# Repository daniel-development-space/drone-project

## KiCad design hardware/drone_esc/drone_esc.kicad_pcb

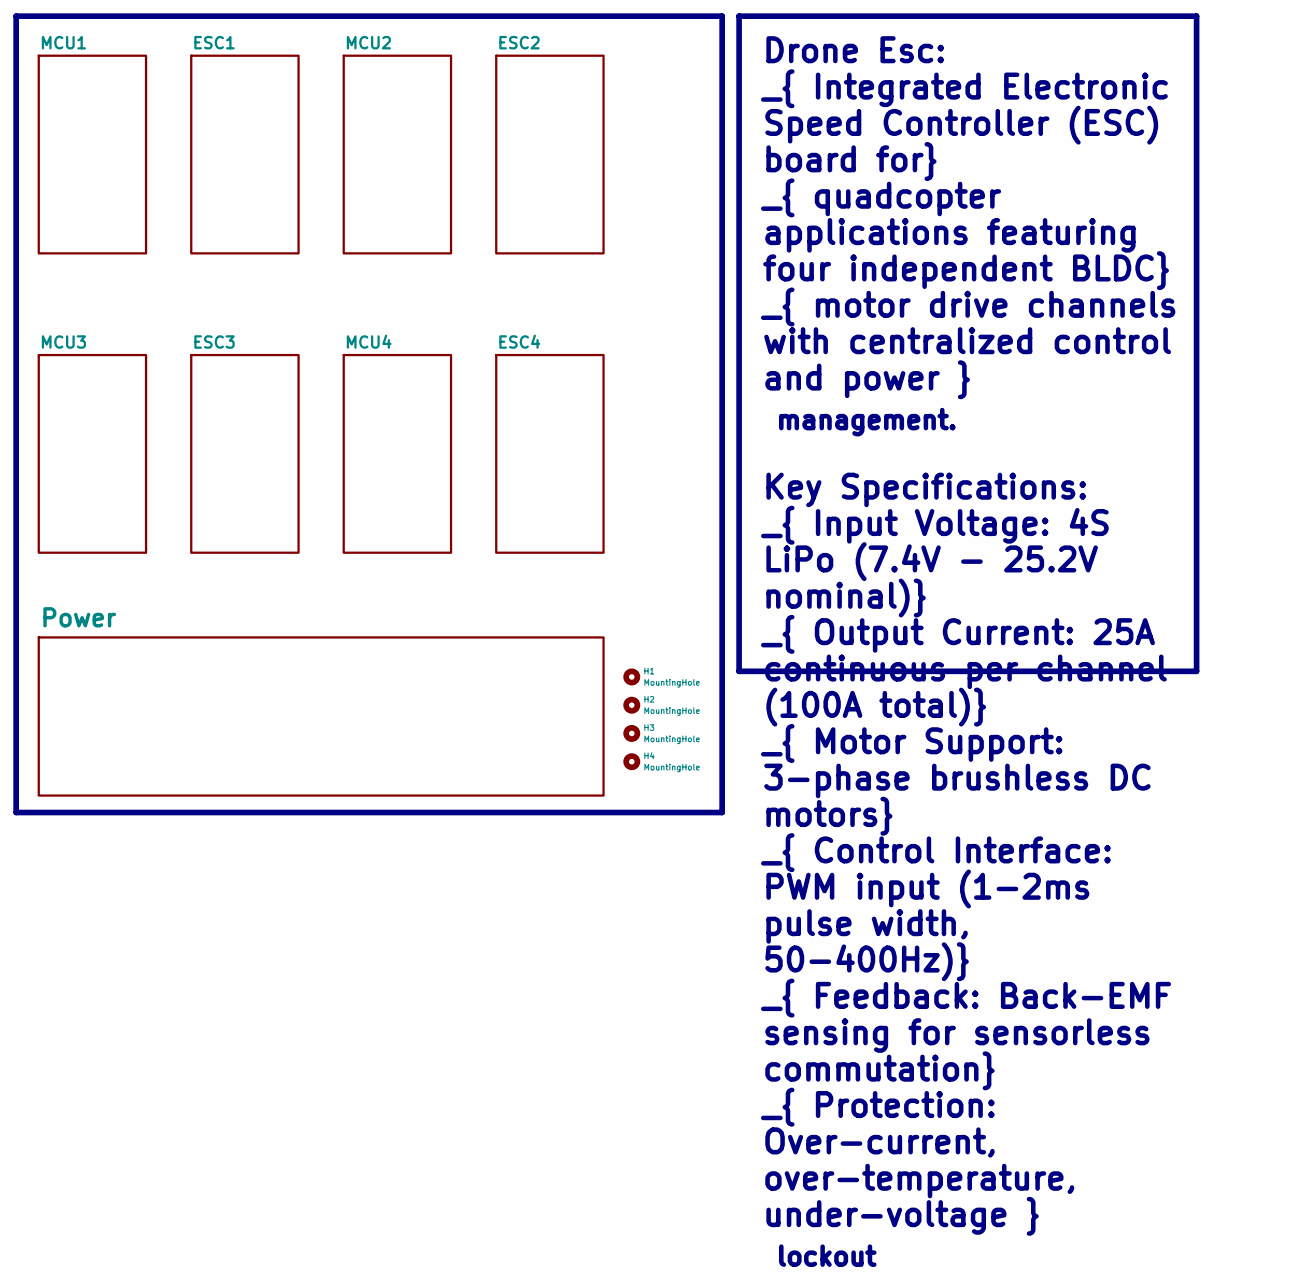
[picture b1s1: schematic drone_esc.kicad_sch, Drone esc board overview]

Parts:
H1, H2, H3, H4: MountingHole; MountingHole_3.2mm_M3

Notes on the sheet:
Drone Esc: _{ Integrated Electronic Speed Controller (ESC) board for} _{ quadcopter applications featuring four independent BLDC} _{ motor drive channels with centralized control and power } _{ management.} Key Specifications: _{ Input Voltage: 4S LiPo (7.4V - 25.2V nominal)} _{ Output Current: 25A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

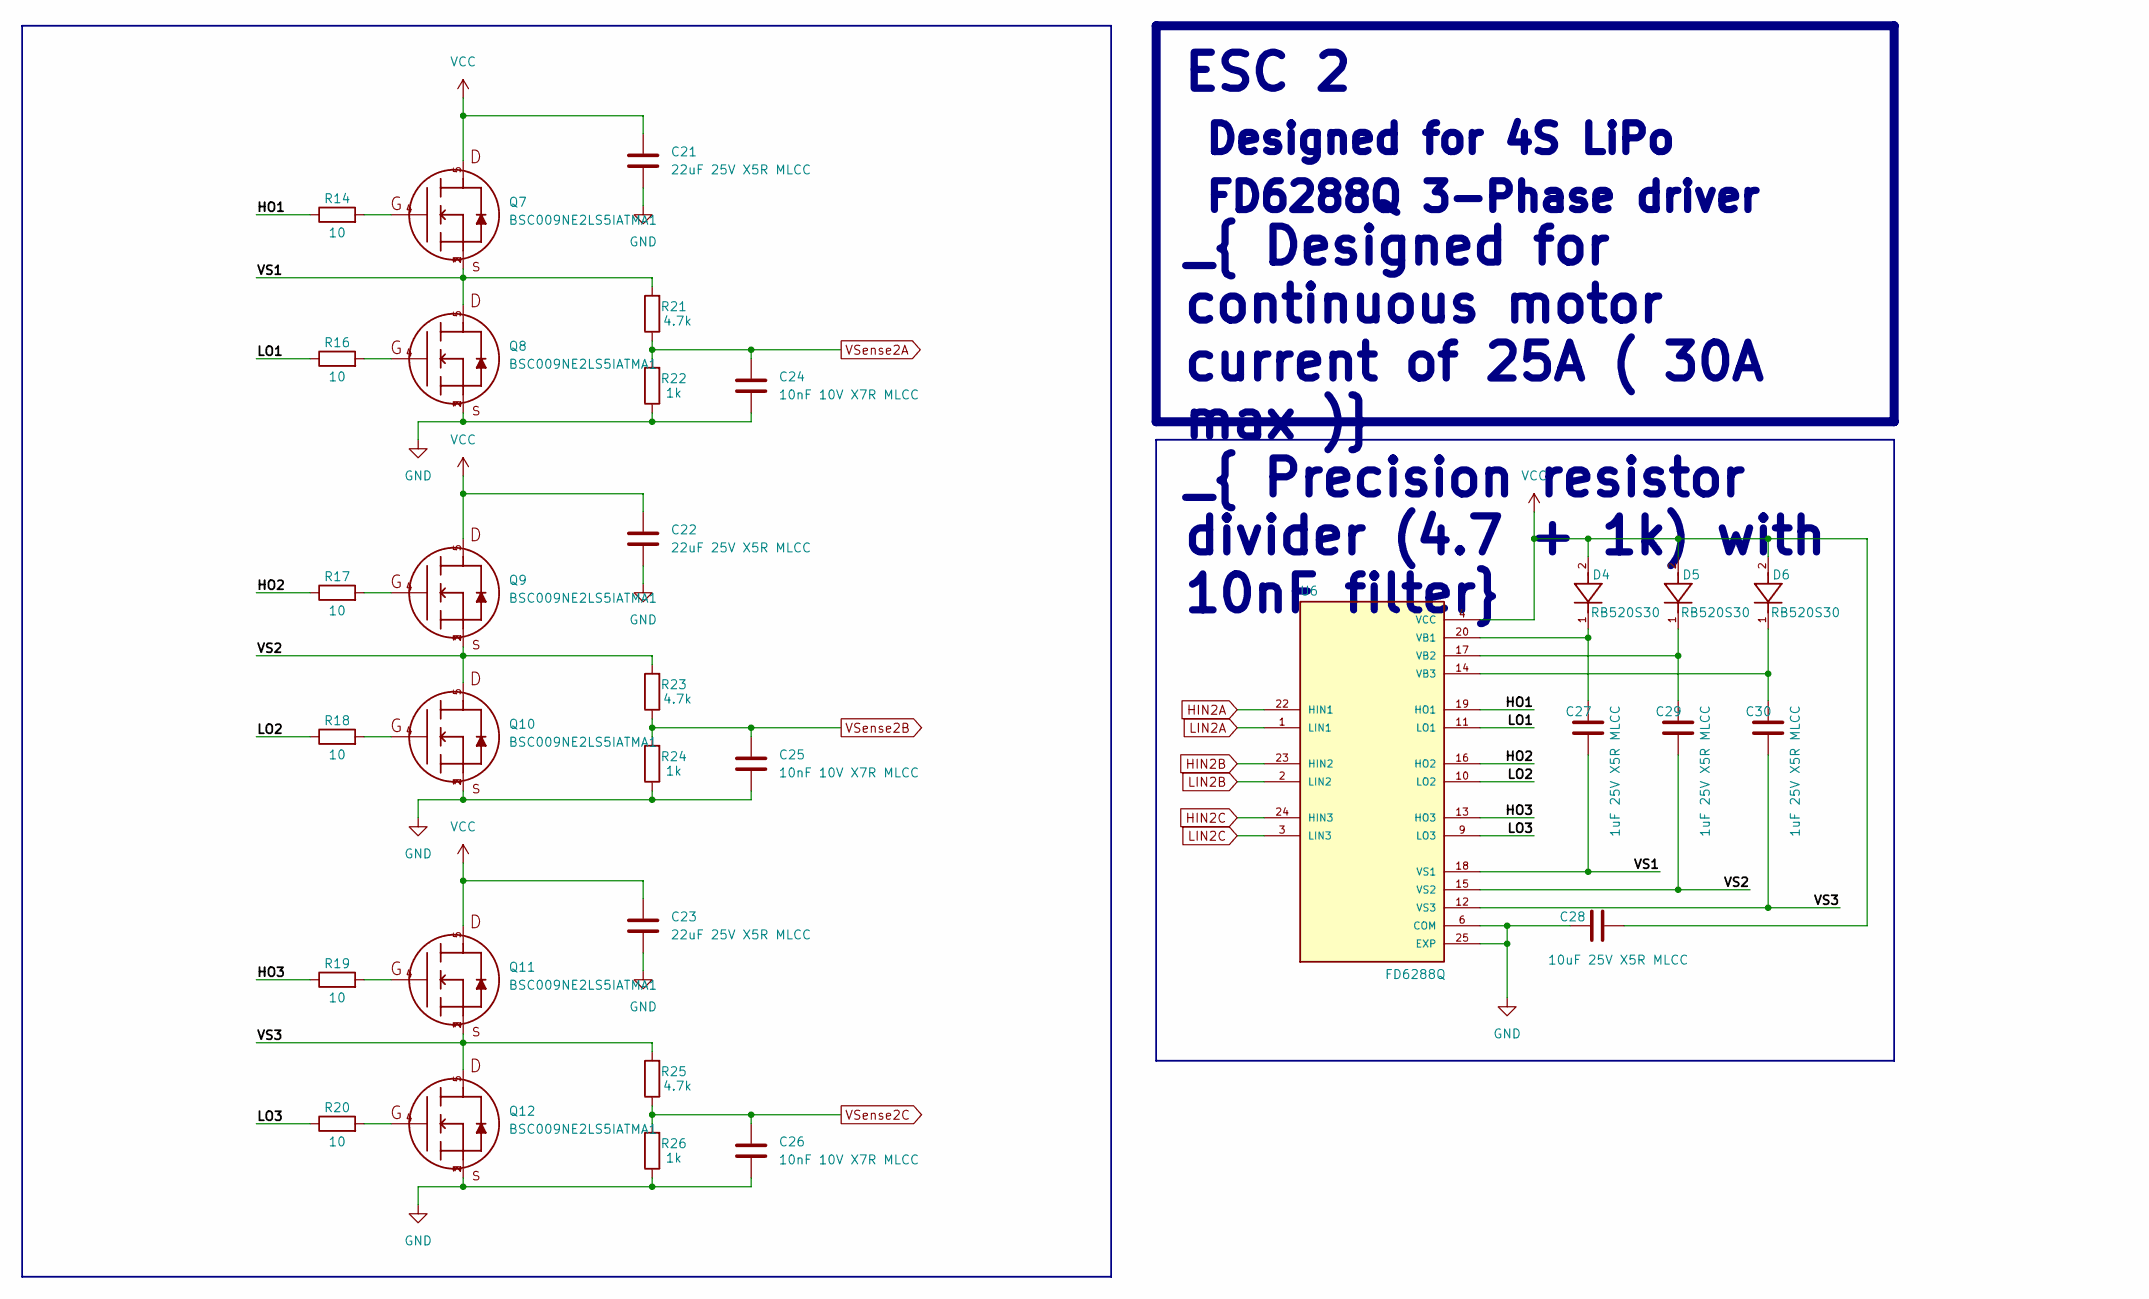
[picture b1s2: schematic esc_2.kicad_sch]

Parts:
C21, C22, C23: 22uF 25V X5R MLCC; C_0805_2012Metric; JLCPCB part C45783
C24, C25, C26: 10nF 10V X7R MLCC; C_0402_1005Metric; JLCPCB part C15195
C27, C29, C30: 1uF 25V X5R MLCC; C_0402_1005Metric; JLCPCB part C52923
C28: 10uF 25V X5R MLCC; C_0603_1608Metric; JLCPCB part C96446
D4, D5, D6: RB520S30; JLCPCB part C8522
Q7, Q8, Q9, Q10, Q11, Q12: BSC009NE2LS5IATMA1; BSC093N04LSGATMA1; JLCPCB part C122543
R14, R16, R17, R18, R19, R20: 10; R_0201_0603Metric; JLCPCB part C105889
R21, R23, R25: 4.7k; R_0402_1005Metric; JLCPCB part C25900
R22, R24, R26: 1k; R_0402_1005Metric; JLCPCB part C11702
U6: FD6288Q; JLCPCB part C328453

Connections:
/ESC2/HO1: R14.1, U6.19 (HO1)
/ESC2/HO2: R17.1, U6.16 (HO2)
/ESC2/HO3: R19.1, U6.13 (HO3)
/ESC2/LO1: R16.1, U6.11 (LO1)
/ESC2/LO2: R18.1, U6.10 (LO2)
/ESC2/LO3: R20.1, U6.9 (LO3)
/ESC2/VS1: C27.2, Q7.1, Q7.2, Q7.3, Q8.5, R21.2, U6.18 (VS1)
/ESC2/VS2: C29.2, Q9.1, Q9.2, Q9.3, Q10.5, R23.2, U6.15 (VS2)
/ESC2/VS3: C30.2, Q11.1, Q11.2, Q11.3, Q12.5, R25.2, U6.12 (VS3)
GND: C21.2, C22.2, C23.2, C24.2, C25.2, C26.2, C28.1, Q8.1, Q8.2, Q8.3, Q10.1, Q10.2, Q10.3, Q12.1, Q12.2, Q12.3, R22.1, R24.1, R26.1, U6.6 (COM), U6.25 (EXP); also elsewhere on the board
HIN2A: U6.22 (HIN1); also elsewhere on the board
HIN2B: U6.23 (HIN2); also elsewhere on the board
HIN2C: U6.24 (HIN3); also elsewhere on the board
LIN2A: U6.1 (LIN1); also elsewhere on the board
LIN2B: U6.2 (LIN2); also elsewhere on the board
LIN2C: U6.3 (LIN3); also elsewhere on the board
unnamed: Q7.4, R14.2
unnamed: Q8.4, R16.2
unnamed: Q9.4, R17.2
unnamed: Q10.4, R18.2
unnamed: Q11.4, R19.2
unnamed: Q12.4, R20.2
unnamed: C27.1, D4.1, U6.20 (VB1)
unnamed: C29.1, D5.1, U6.17 (VB2)
unnamed: C30.1, D6.1, U6.14 (VB3)
VCC: C21.1, C22.1, C23.1, C28.2, D4.2, D5.2, D6.2, Q7.5, Q9.5, Q11.5, U6.4 (VCC); also elsewhere on the board
VSense2A: C24.1, R21.1, R22.2; also elsewhere on the board
VSense2B: C25.1, R23.1, R24.2; also elsewhere on the board
VSense2C: C26.1, R25.1, R26.2; also elsewhere on the board

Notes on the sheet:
ESC 2 _{ Designed for 4S LiPo} _{ FD6288Q 3-Phase driver} _{ Designed for continuous motor current of 25A ( 30A max )} _{ Precision resistor divider (4.7 + 1k) with 10nF filter}

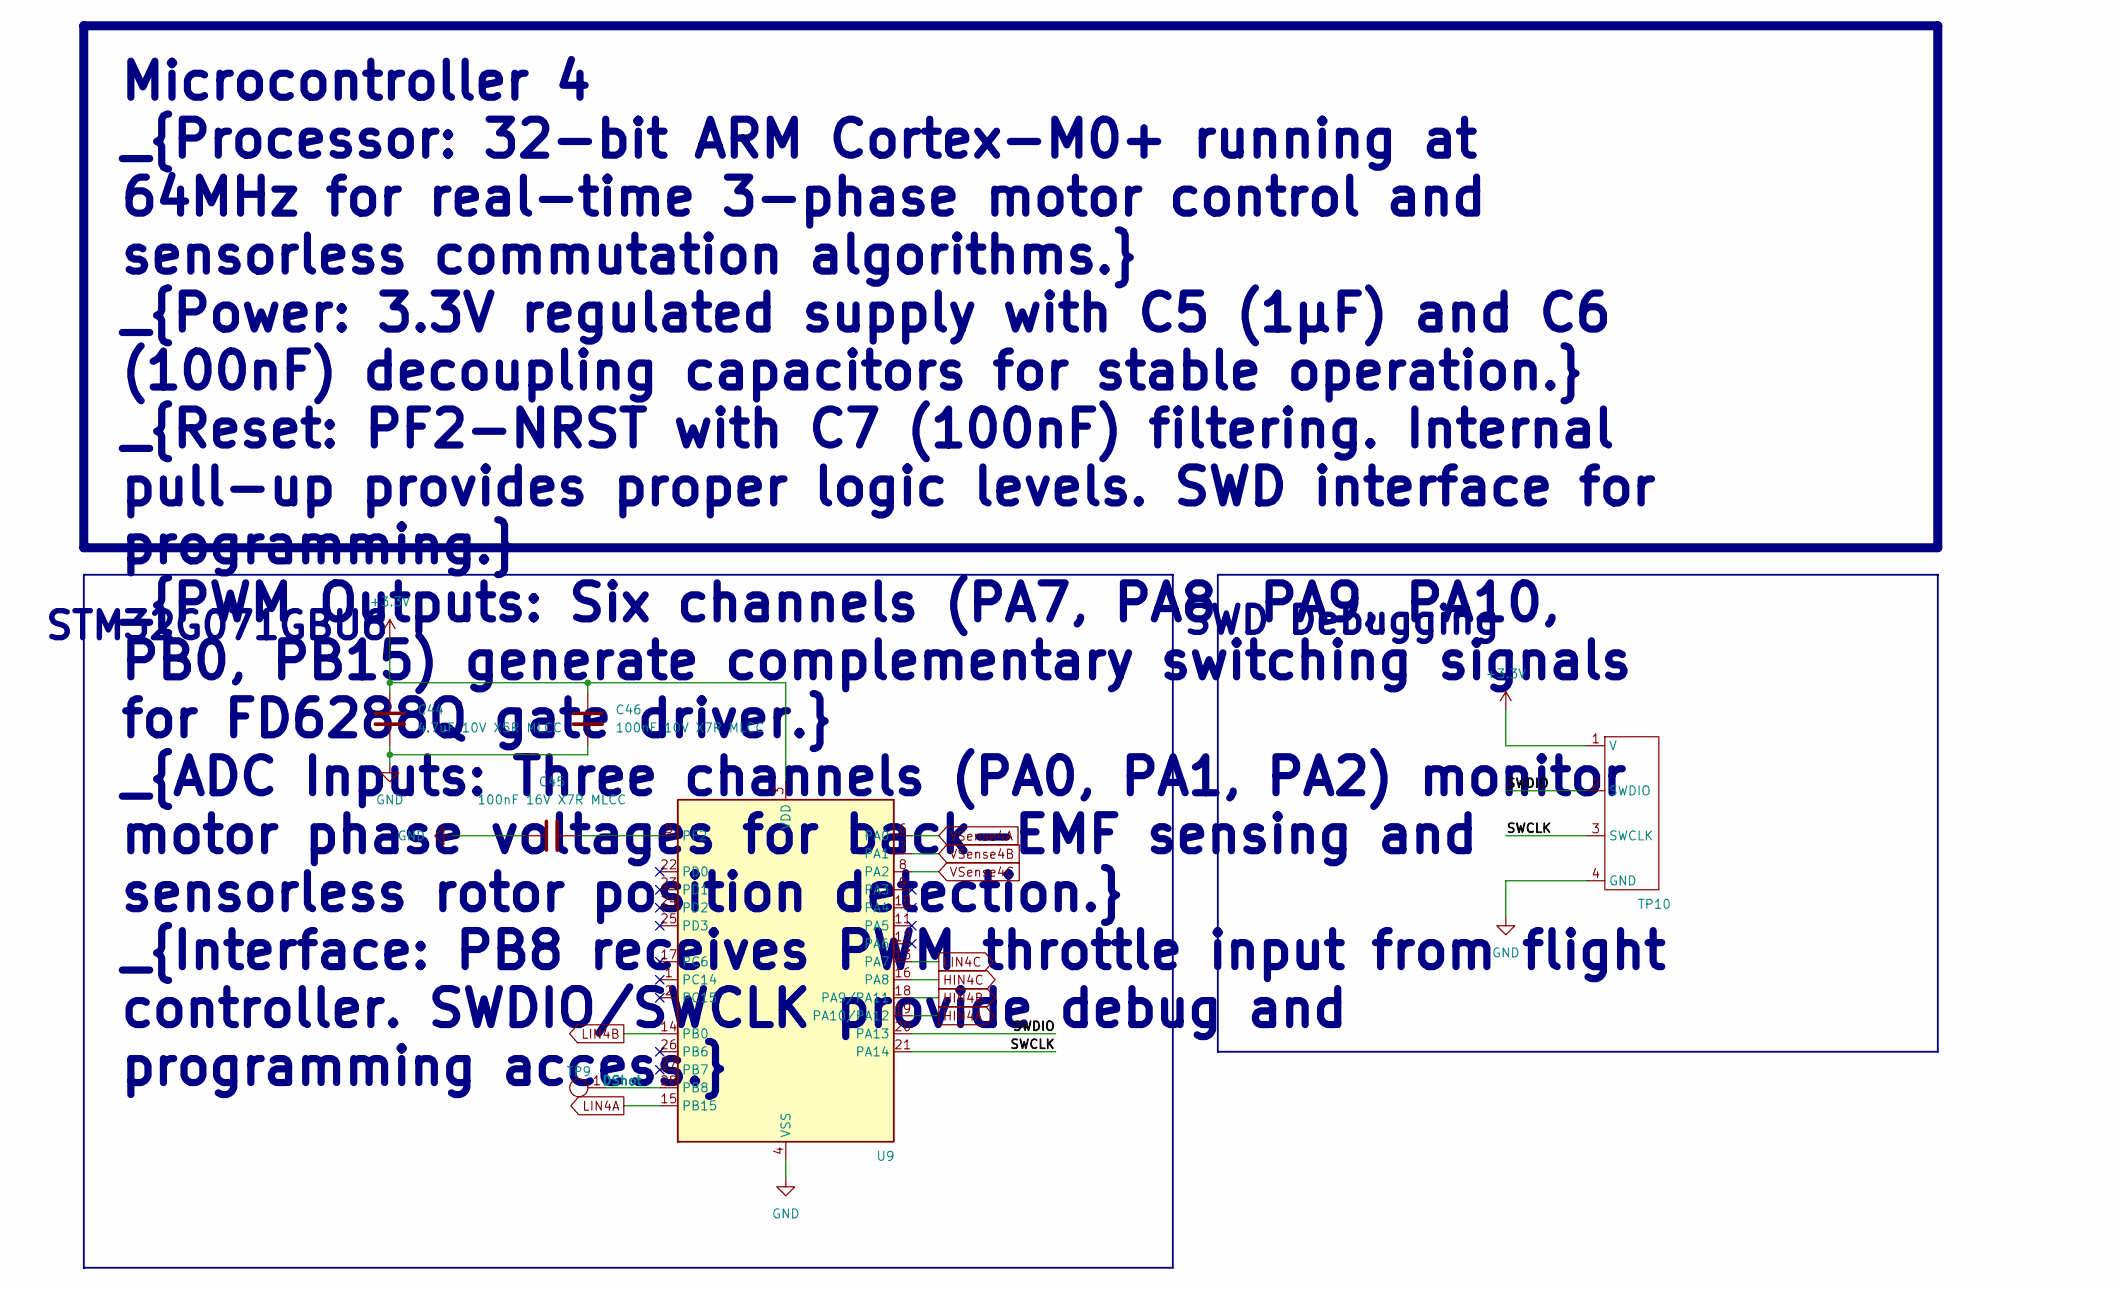
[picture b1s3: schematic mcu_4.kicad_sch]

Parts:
C44: 4.7uF 10V X5R MLCC; C_0402_1005Metric; JLCPCB part C23733
C45: 100nF 16V X7R MLCC; C_0402_1005Metric; JLCPCB part C307331
C46: 100nF 10V X7R MLCC; C_0402_1005Metric; JLCPCB part C307331
TP9: DShot; Rectangle test point
TP10: 1.27 test pad
U9: STM32G071GBU6; QFN-28_4x4mm_P0.5mm; JLCPCB part C529347

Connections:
+3.3V: C44.1, C46.1, TP10.1 (V), U9.3 (VDD); also elsewhere on the board
/MCU4/SWCLK: TP10.3 (SWCLK), U9.21 (PA14)
/MCU4/SWDIO: TP10.2 (SWDIO), U9.20 (PA13)
GND: C44.2, C45.1, C46.2, TP10.4 (GND), U9.4 (VSS); also elsewhere on the board
HIN4A: U9.19 (PA10/PA12); also elsewhere on the board
HIN4B: U9.18 (PA9/PA11); also elsewhere on the board
HIN4C: U9.16 (PA8); also elsewhere on the board
LIN4A: U9.15 (PB15); also elsewhere on the board
LIN4B: U9.14 (PB0); also elsewhere on the board
LIN4C: U9.13 (PA7); also elsewhere on the board
unnamed: TP9.1, U9.28 (PB8)
unnamed: C45.2, U9.5 (PF2)
VSense4A: U9.6 (PA0); also elsewhere on the board
VSense4B: U9.7 (PA1); also elsewhere on the board
VSense4C: U9.8 (PA2); also elsewhere on the board

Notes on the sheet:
SWD Debugging
STM32G071GBU6
Microcontroller 4 _{Processor: 32-bit ARM Cortex-M0+ running at 64MHz for real-time 3-phase motor control and sensorless commutation algorithms.} _{Power: 3.3V regulated supply with C5 (1µF) and C6 (100nF) decoupling capacitors for stable operation.} _{Reset: PF2-NRST with C7 (100nF) filtering. Int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

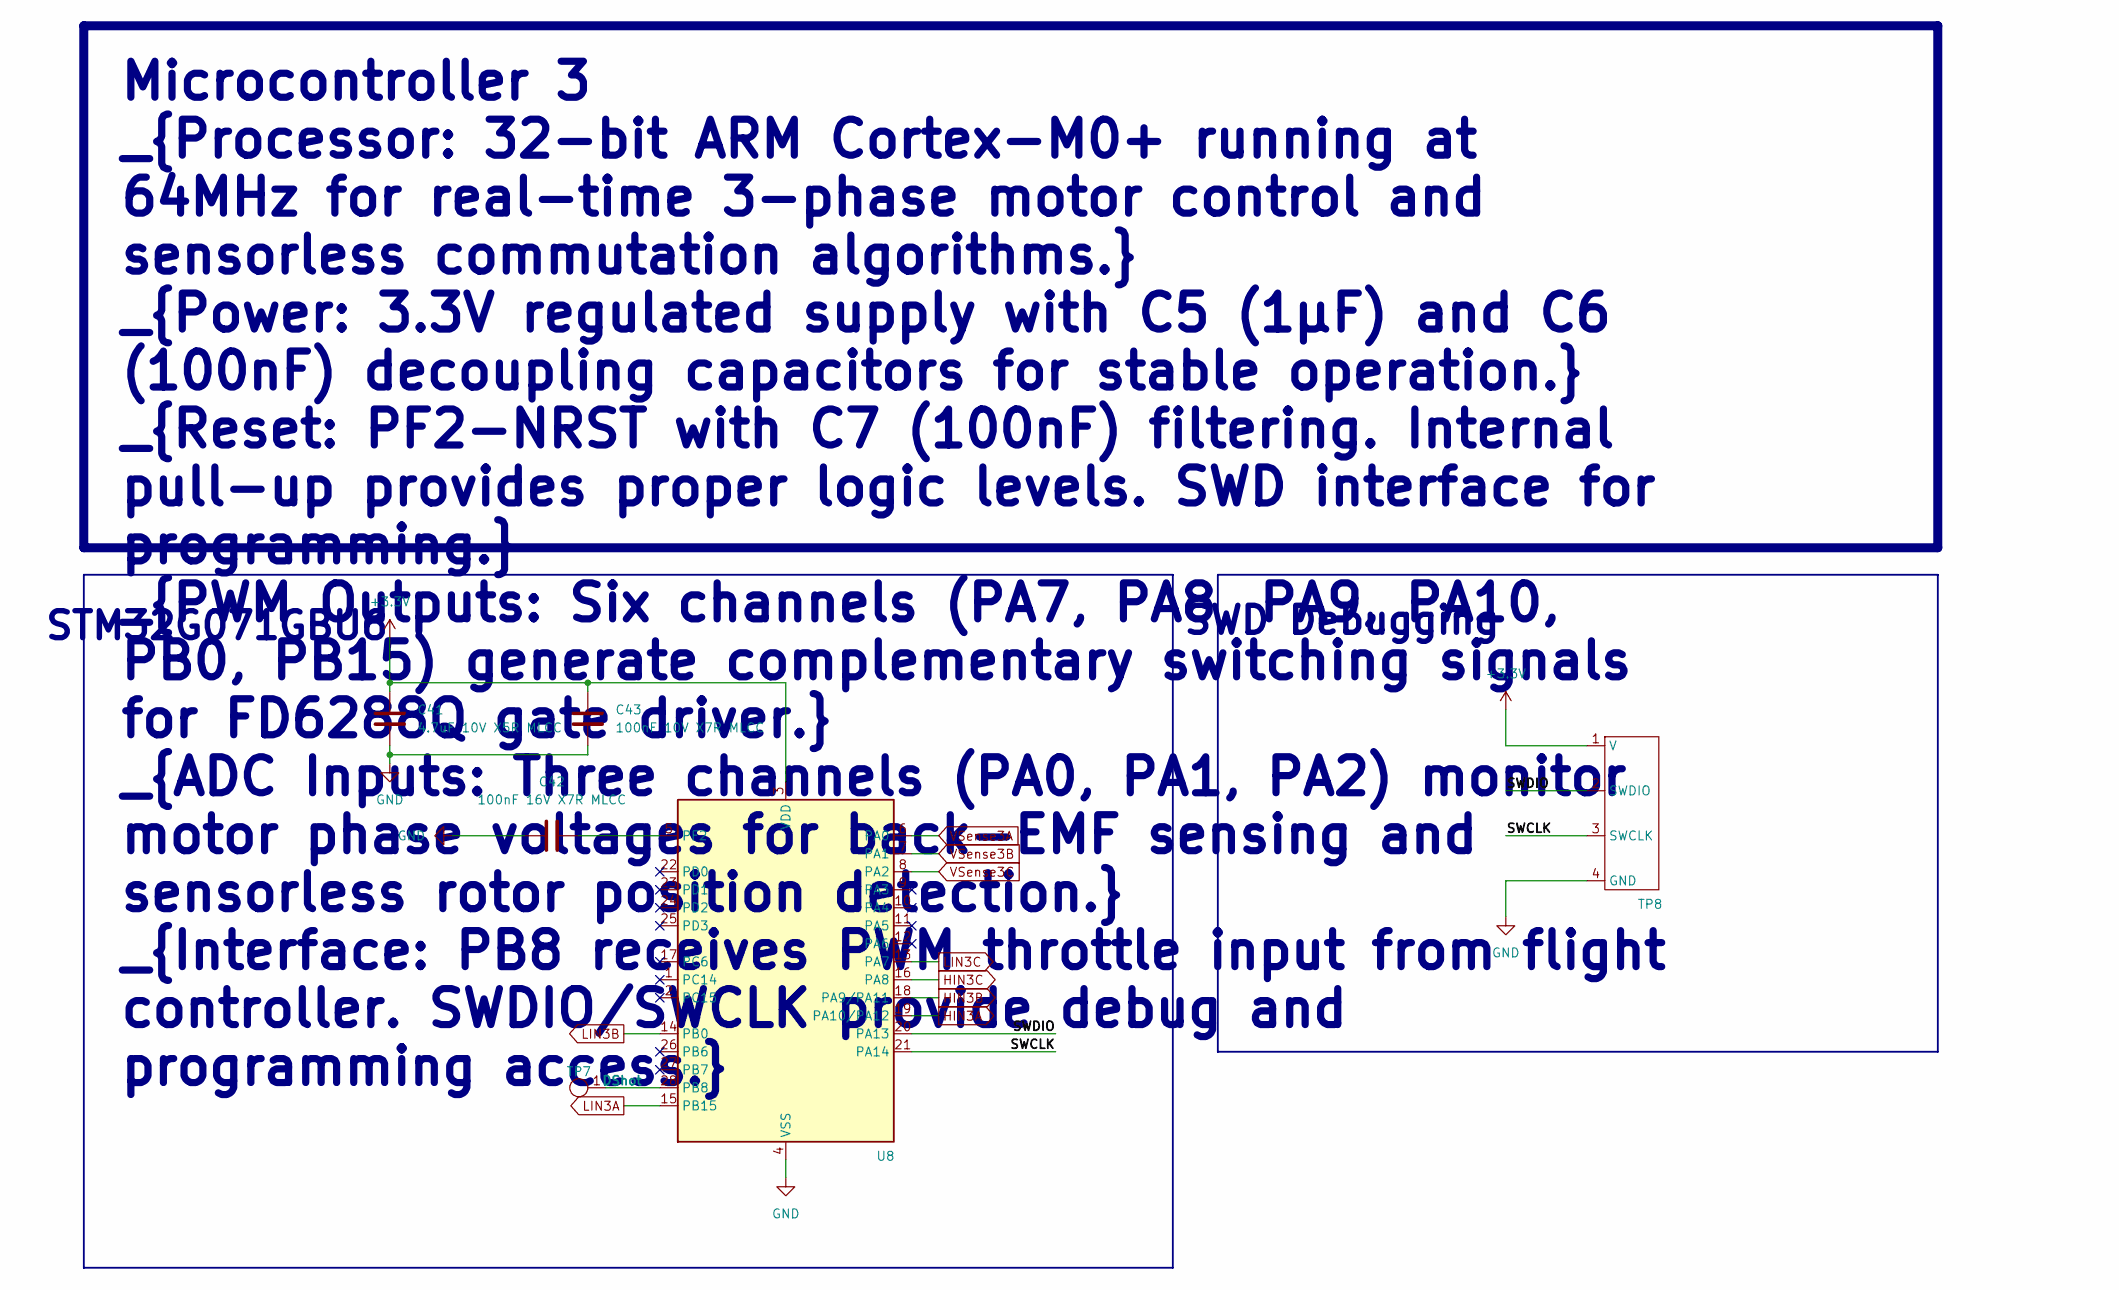
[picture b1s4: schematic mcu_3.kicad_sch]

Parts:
C41: 4.7uF 10V X5R MLCC; C_0402_1005Metric; JLCPCB part C23733
C42: 100nF 16V X7R MLCC; C_0402_1005Metric; JLCPCB part C307331
C43: 100nF 10V X7R MLCC; C_0402_1005Metric; JLCPCB part C307331
TP7: DShot; Rectangle test point
TP8: 1.27 test pad
U8: STM32G071GBU6; QFN-28_4x4mm_P0.5mm; JLCPCB part C529347

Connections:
+3.3V: C41.1, C43.1, TP8.1 (V), U8.3 (VDD); also elsewhere on the board
/MCU3/SWCLK: TP8.3 (SWCLK), U8.21 (PA14)
/MCU3/SWDIO: TP8.2 (SWDIO), U8.20 (PA13)
GND: C41.2, C42.1, C43.2, TP8.4 (GND), U8.4 (VSS); also elsewhere on the board
HIN3A: U8.19 (PA10/PA12); also elsewhere on the board
HIN3B: U8.18 (PA9/PA11); also elsewhere on the board
HIN3C: U8.16 (PA8); also elsewhere on the board
LIN3A: U8.15 (PB15); also elsewhere on the board
LIN3B: U8.14 (PB0); also elsewhere on the board
LIN3C: U8.13 (PA7); also elsewhere on the board
unnamed: TP7.1, U8.28 (PB8)
unnamed: C42.2, U8.5 (PF2)
VSense3A: U8.6 (PA0); also elsewhere on the board
VSense3B: U8.7 (PA1); also elsewhere on the board
VSense3C: U8.8 (PA2); also elsewhere on the board

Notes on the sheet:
SWD Debugging
STM32G071GBU6
Microcontroller 3 _{Processor: 32-bit ARM Cortex-M0+ running at 64MHz for real-time 3-phase motor control and sensorless commutation algorithms.} _{Power: 3.3V regulated supply with C5 (1µF) and C6 (100nF) decoupling capacitors for stable operation.} _{Reset: PF2-NRST with C7 (100nF) filtering. Int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

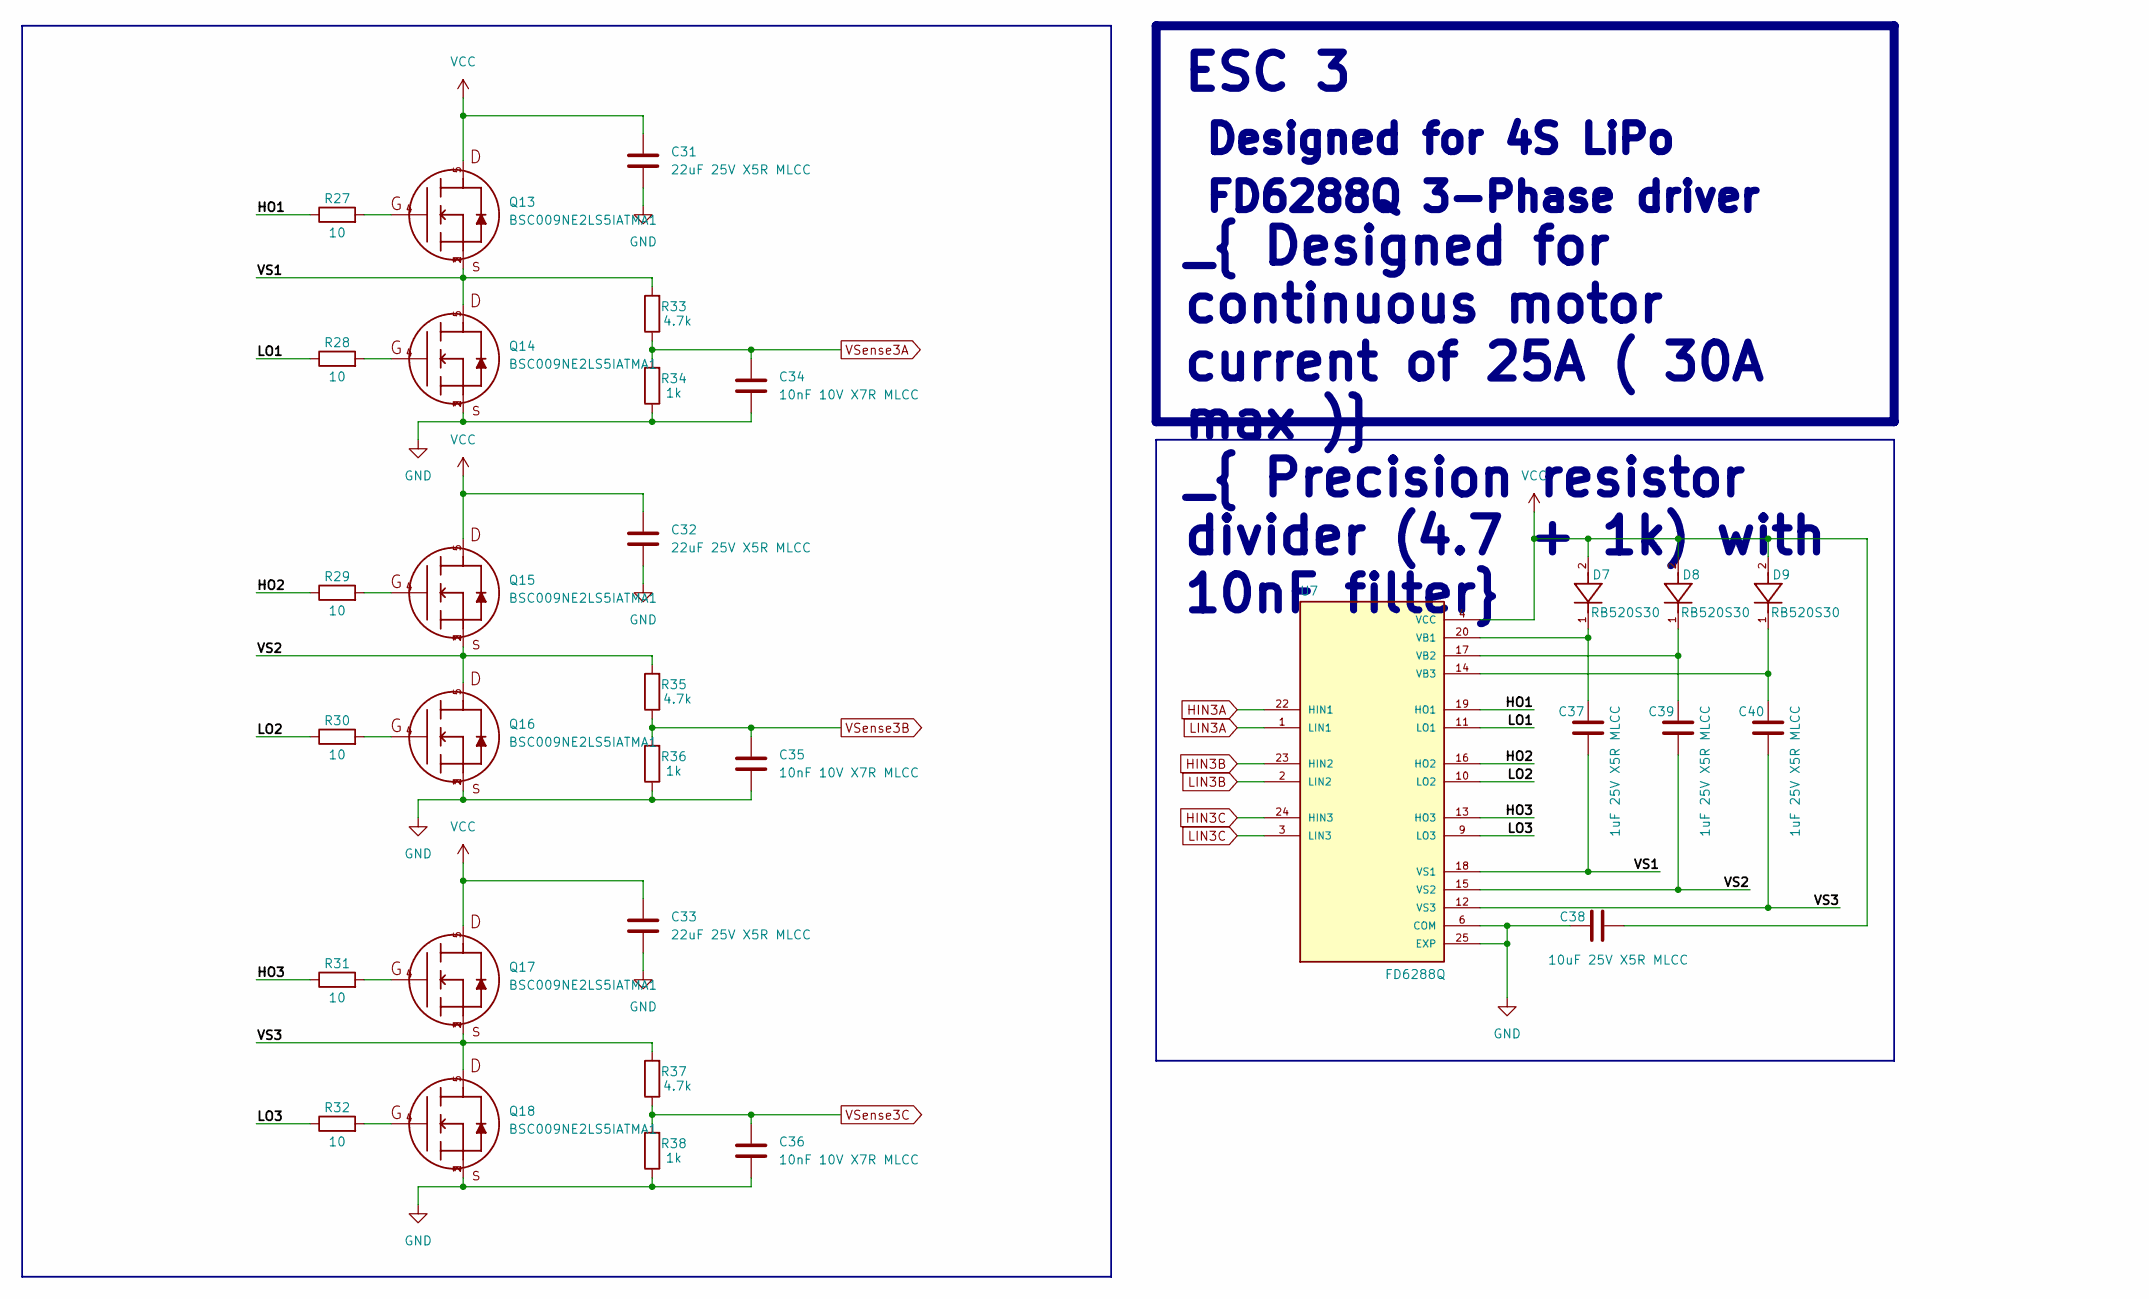
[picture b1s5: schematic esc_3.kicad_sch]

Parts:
C31, C32, C33: 22uF 25V X5R MLCC; C_0805_2012Metric; JLCPCB part C45783
C34, C35, C36: 10nF 10V X7R MLCC; C_0402_1005Metric; JLCPCB part C15195
C37, C39, C40: 1uF 25V X5R MLCC; C_0402_1005Metric; JLCPCB part C52923
C38: 10uF 25V X5R MLCC; C_0603_1608Metric; JLCPCB part C96446
D7, D8, D9: RB520S30; JLCPCB part C8522
Q13, Q14, Q15, Q16, Q17, Q18: BSC009NE2LS5IATMA1; BSC093N04LSGATMA1; JLCPCB part C122543
R27, R28, R29, R30, R31, R32: 10; R_0201_0603Metric; JLCPCB part C105889
R33, R35, R37: 4.7k; R_0402_1005Metric; JLCPCB part C25900
R34, R36, R38: 1k; R_0402_1005Metric; JLCPCB part C11702
U7: FD6288Q; JLCPCB part C328453

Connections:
/ESC3/HO1: R27.1, U7.19 (HO1)
/ESC3/HO2: R29.1, U7.16 (HO2)
/ESC3/HO3: R31.1, U7.13 (HO3)
/ESC3/LO1: R28.1, U7.11 (LO1)
/ESC3/LO2: R30.1, U7.10 (LO2)
/ESC3/LO3: R32.1, U7.9 (LO3)
/ESC3/VS1: C37.2, Q13.1, Q13.2, Q13.3, Q14.5, R33.2, U7.18 (VS1)
/ESC3/VS2: C39.2, Q15.1, Q15.2, Q15.3, Q16.5, R35.2, U7.15 (VS2)
/ESC3/VS3: C40.2, Q17.1, Q17.2, Q17.3, Q18.5, R37.2, U7.12 (VS3)
GND: C31.2, C32.2, C33.2, C34.2, C35.2, C36.2, C38.1, Q14.1, Q14.2, Q14.3, Q16.1, Q16.2, Q16.3, Q18.1, Q18.2, Q18.3, R34.1, R36.1, R38.1, U7.6 (COM), U7.25 (EXP); also elsewhere on the board
HIN3A: U7.22 (HIN1); also elsewhere on the board
HIN3B: U7.23 (HIN2); also elsewhere on the board
HIN3C: U7.24 (HIN3); also elsewhere on the board
LIN3A: U7.1 (LIN1); also elsewhere on the board
LIN3B: U7.2 (LIN2); also elsewhere on the board
LIN3C: U7.3 (LIN3); also elsewhere on the board
unnamed: Q13.4, R27.2
unnamed: Q14.4, R28.2
unnamed: Q15.4, R29.2
unnamed: Q16.4, R30.2
unnamed: Q17.4, R31.2
unnamed: Q18.4, R32.2
unnamed: C37.1, D7.1, U7.20 (VB1)
unnamed: C39.1, D8.1, U7.17 (VB2)
unnamed: C40.1, D9.1, U7.14 (VB3)
VCC: C31.1, C32.1, C33.1, C38.2, D7.2, D8.2, D9.2, Q13.5, Q15.5, Q17.5, U7.4 (VCC); also elsewhere on the board
VSense3A: C34.1, R33.1, R34.2; also elsewhere on the board
VSense3B: C35.1, R35.1, R36.2; also elsewhere on the board
VSense3C: C36.1, R37.1, R38.2; also elsewhere on the board

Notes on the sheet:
ESC 3 _{ Designed for 4S LiPo} _{ FD6288Q 3-Phase driver} _{ Designed for continuous motor current of 25A ( 30A max )} _{ Precision resistor divider (4.7 + 1k) with 10nF filter}

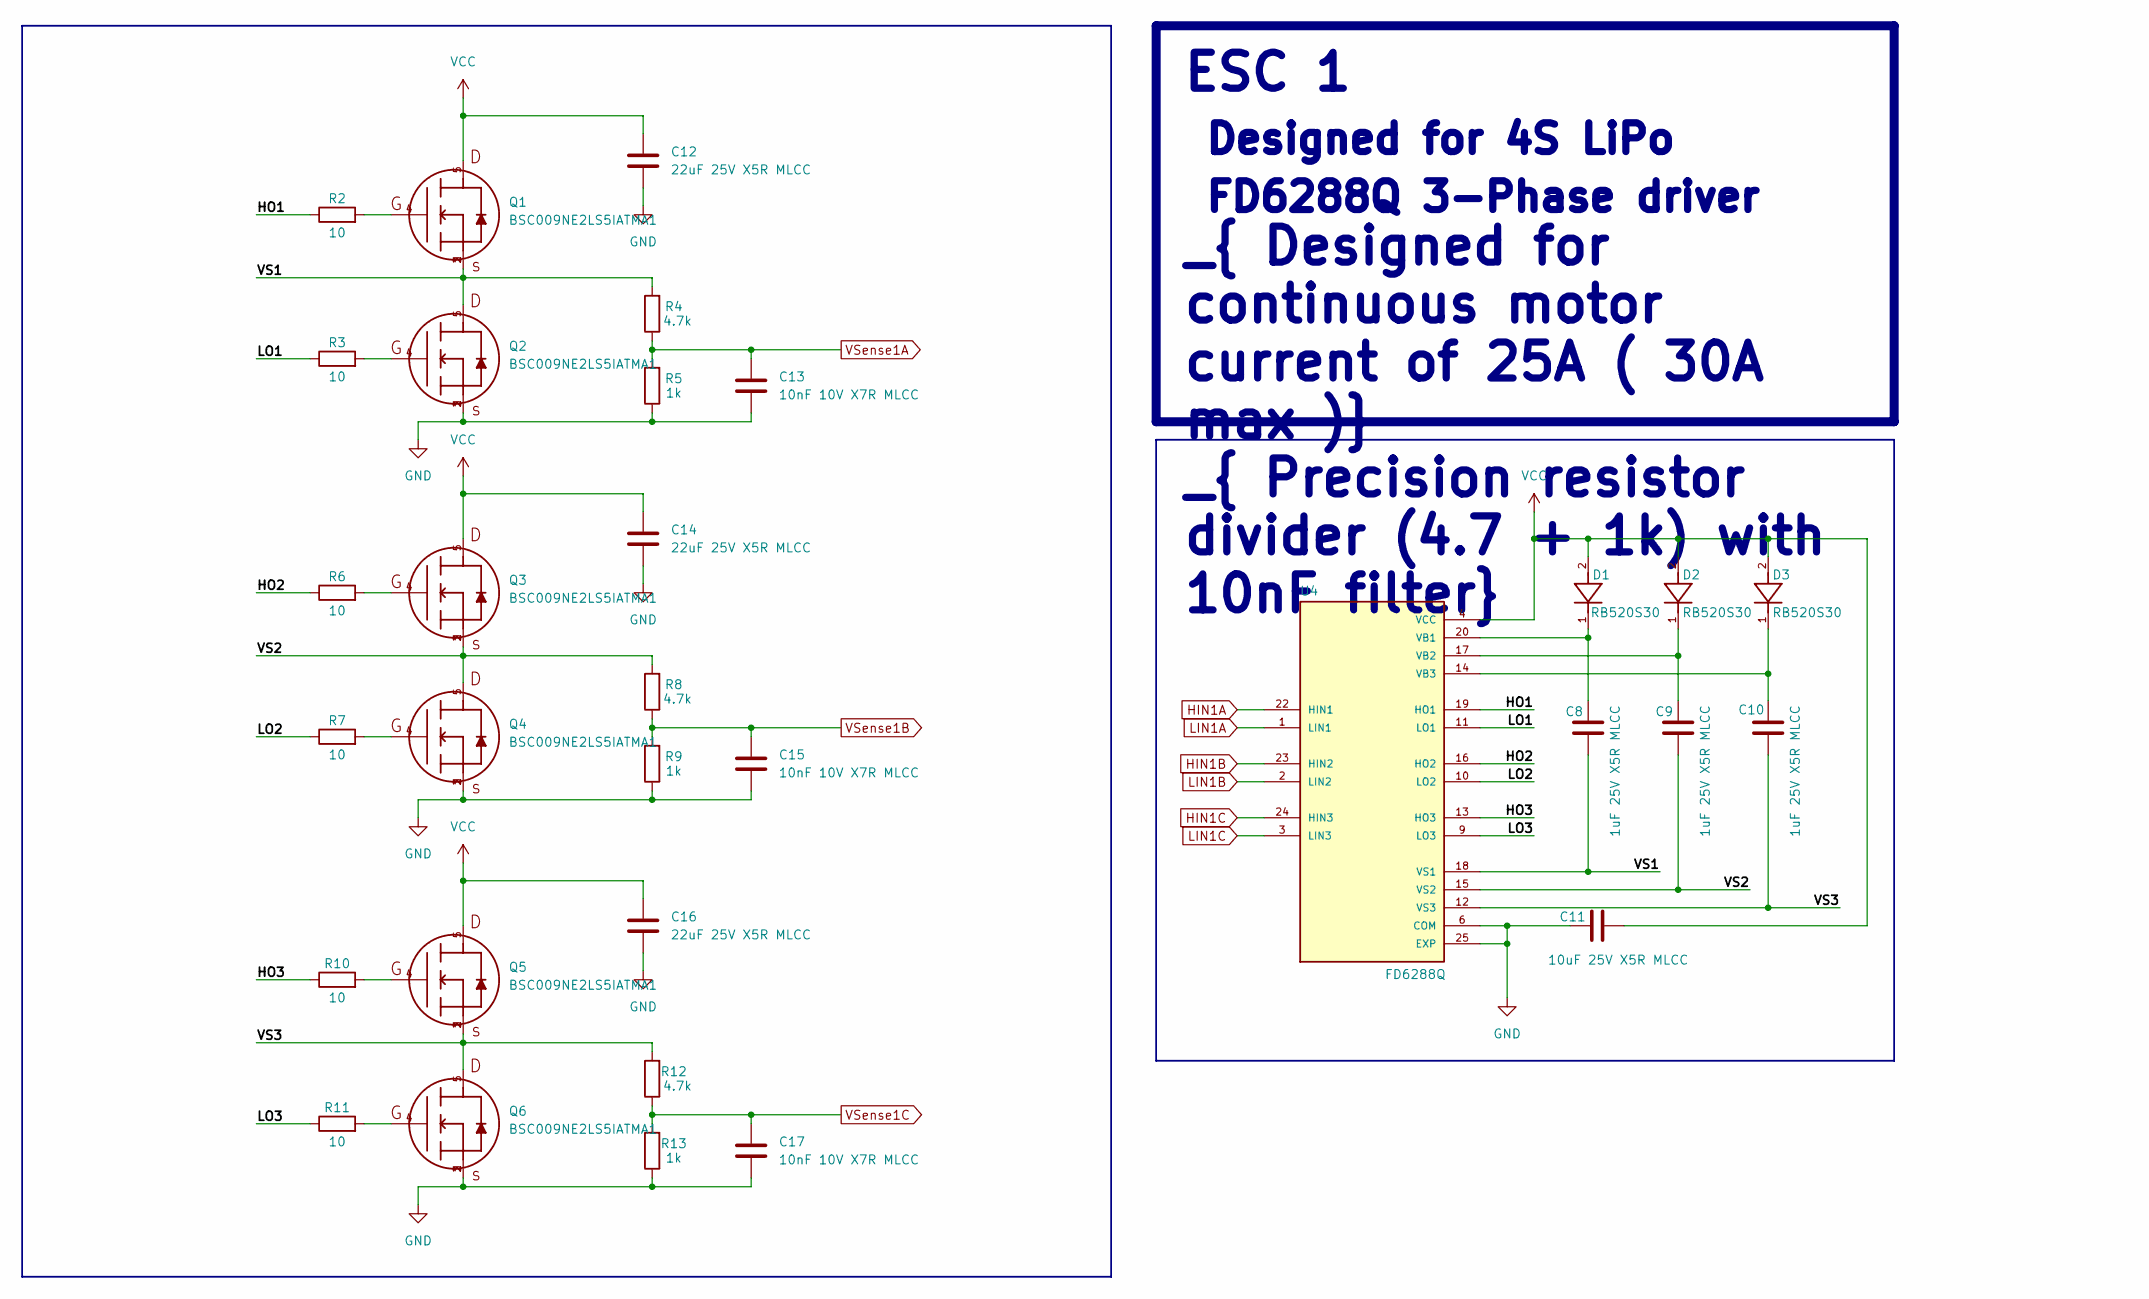
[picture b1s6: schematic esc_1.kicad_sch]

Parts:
C8, C9, C10: 1uF 25V X5R MLCC; C_0402_1005Metric; JLCPCB part C52923
C11: 10uF 25V X5R MLCC; C_0603_1608Metric; JLCPCB part C96446
C12, C14, C16: 22uF 25V X5R MLCC; C_0805_2012Metric; JLCPCB part C45783
C13, C15, C17: 10nF 10V X7R MLCC; C_0402_1005Metric; JLCPCB part C15195
D1, D2, D3: RB520S30; JLCPCB part C8522
Q1, Q2, Q3, Q4, Q5, Q6: BSC009NE2LS5IATMA1; BSC093N04LSGATMA1; JLCPCB part C122543
R2, R3, R6, R7, R10, R11: 10; R_0201_0603Metric; JLCPCB part C105889
R4, R8, R12: 4.7k; R_0402_1005Metric; JLCPCB part C25900
R5, R9, R13: 1k; R_0402_1005Metric; JLCPCB part C11702
U4: FD6288Q; JLCPCB part C328453

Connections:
/ESC1/HO1: R2.1, U4.19 (HO1)
/ESC1/HO2: R6.1, U4.16 (HO2)
/ESC1/HO3: R10.1, U4.13 (HO3)
/ESC1/LO1: R3.1, U4.11 (LO1)
/ESC1/LO2: R7.1, U4.10 (LO2)
/ESC1/LO3: R11.1, U4.9 (LO3)
/ESC1/VS1: C8.2, Q1.1, Q1.2, Q1.3, Q2.5, R4.2, U4.18 (VS1)
/ESC1/VS2: C9.2, Q3.1, Q3.2, Q3.3, Q4.5, R8.2, U4.15 (VS2)
/ESC1/VS3: C10.2, Q5.1, Q5.2, Q5.3, Q6.5, R12.2, U4.12 (VS3)
GND: C11.1, C12.2, C13.2, C14.2, C15.2, C16.2, C17.2, Q2.1, Q2.2, Q2.3, Q4.1, Q4.2, Q4.3, Q6.1, Q6.2, Q6.3, R5.1, R9.1, R13.1, U4.6 (COM), U4.25 (EXP); also elsewhere on the board
HIN1A: U4.22 (HIN1); also elsewhere on the board
HIN1B: U4.23 (HIN2); also elsewhere on the board
HIN1C: U4.24 (HIN3); also elsewhere on the board
LIN1A: U4.1 (LIN1); also elsewhere on the board
LIN1B: U4.2 (LIN2); also elsewhere on the board
LIN1C: U4.3 (LIN3); also elsewhere on the board
unnamed: Q1.4, R2.2
unnamed: Q2.4, R3.2
unnamed: Q3.4, R6.2
unnamed: Q4.4, R7.2
unnamed: Q5.4, R10.2
unnamed: Q6.4, R11.2
unnamed: C8.1, D1.1, U4.20 (VB1)
unnamed: C9.1, D2.1, U4.17 (VB2)
unnamed: C10.1, D3.1, U4.14 (VB3)
VCC: C11.2, C12.1, C14.1, C16.1, D1.2, D2.2, D3.2, Q1.5, Q3.5, Q5.5, U4.4 (VCC); also elsewhere on the board
VSense1A: C13.1, R4.1, R5.2; also elsewhere on the board
VSense1B: C15.1, R8.1, R9.2; also elsewhere on the board
VSense1C: C17.1, R12.1, R13.2; also elsewhere on the board

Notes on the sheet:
ESC 1 _{ Designed for 4S LiPo} _{ FD6288Q 3-Phase driver} _{ Designed for continuous motor current of 25A ( 30A max )} _{ Precision resistor divider (4.7 + 1k) with 10nF filter}
